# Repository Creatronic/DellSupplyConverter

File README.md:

# DellSupplyConverter
 Transform your old Dell charger to be usable on new Dell laptop
 
# About hardware
* PCB before 1.3 have been tested and are not ok against Dell connector footprint.
* V1.3 has not been tested yet (I hope it's the good one this time ...)
 
 # More infos
 https://blog.creatronic.fr/hacker-les-chargeurs-dell/

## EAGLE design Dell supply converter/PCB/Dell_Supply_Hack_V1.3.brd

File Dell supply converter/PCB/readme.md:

V1.0 and V1.1 => bad Dell connector footprint
V1.3 => not tested yet

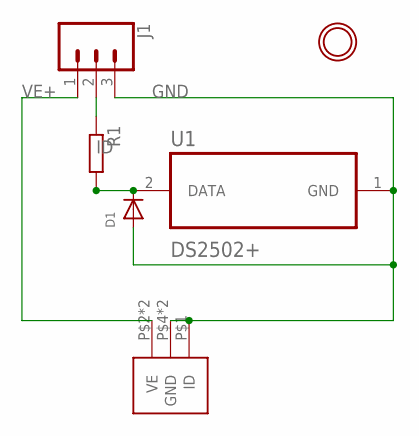
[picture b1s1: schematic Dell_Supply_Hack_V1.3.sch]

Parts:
D1: DIODESOD-323F; SOD-323F
J1: CONN_03LONGPADS; 1X03_LONGPADS
R1: R-EU_R0603; R0603
U1: DS2502+; TO92127P495H695-3
U$1: DELL_CON; DELL_CON_01
U$2: MOUNTING_HOLE; MOUNTINGHOLE_3.0_PLATED

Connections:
GND: D1.A, J1.3, U1.1 (GND), U$1.P$1 (ID), U$1.P$4 (GND), U$1.P$5 (GND)
ID: J1.2, R1.1
unnamed: D1.C, R1.2, U1.2 (DATA)
VE+: J1.1, U$1.P$2 (VE), U$1.P$3 (VE)

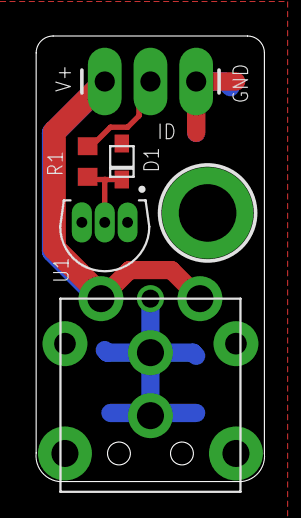
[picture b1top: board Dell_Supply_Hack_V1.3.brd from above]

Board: 2 copper layers, 12.7 x 24.8 mm, 6 parts (0 on the bottom side), 4 nets.

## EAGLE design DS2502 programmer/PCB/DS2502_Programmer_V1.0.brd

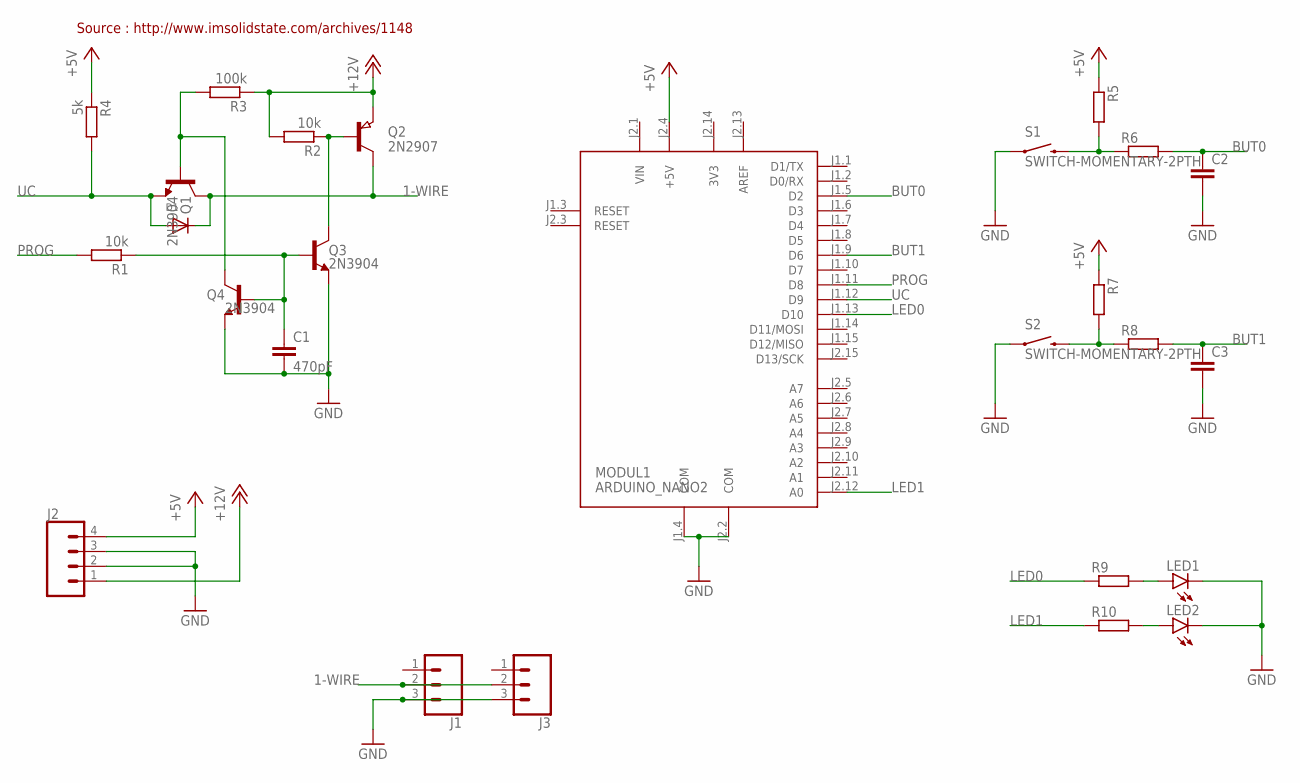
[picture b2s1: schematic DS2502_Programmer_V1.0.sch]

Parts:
C1: 470pF; C0603
C2, C3: C-EUC0603; C0603
D1: DIODESOD-523; SOD-523
J1, J3: CONN_03; 1X03
J2: CONN_04; 1X04
LED1, LED2: LEDCHIP-LED0805; CHIP-LED0805
MODUL1: ARDUINO_NANO2
Q1, Q3, Q4: 2N3904; SOT23-3
Q2: 2N2907; SOT23
R1, R2: 10k; R0603
R3: 100k; R0603
R4: 5k; R0603
R5, R6, R7, R8, R9, R10: R-EU_R0603; R0603
S1, S2: SWITCH-MOMENTARY-2PTH; TACTILE-PTH

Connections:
1-WIRE: D1.K (C), J1.2, J3.2, Q1.3 (C), Q2.3 (C)
3V3: MODUL1.J2.14 (3V3)
+5V: J2.4, MODUL1.J2.4 (+5V), R4.1, R5.1, R7.1
+12V: J2.1, Q2.2 (E), R2.2, R3.1
AREF: MODUL1.J2.13 (AREF)
BUT0: C2.1, MODUL1.J1.5 (D2), R6.2
BUT1: C3.1, MODUL1.J1.9 (D6), R8.2
GND: C1.2, C2.2, C3.2, J1.3, J2.2, J2.3, J3.3, LED1.C, LED2.C, MODUL1.J1.4 (COM), MODUL1.J2.2 (COM), Q3.2 (E), Q4.2 (E), S1.1, S2.1
LED0: MODUL1.J1.13 (D10), R9.1
LED1: MODUL1.J2.12 (A0), R10.1
unnamed: Q2.1 (B), Q3.3 (C), R2.1
unnamed: R5.2, R6.1, S1.3 (2)
unnamed: R7.2, R8.1, S2.3 (2)
unnamed: Q1.1 (B), Q4.3 (C), R3.2
unnamed: LED1.A, R9.2
unnamed: LED2.A, R10.2
unnamed: C1.1, Q3.1 (B), Q4.1 (B), R1.1
PROG: MODUL1.J1.11 (D8), R1.2
UC: D1.A, MODUL1.J1.12 (D9), Q1.2 (E), R4.2
VIN: MODUL1.J2.1 (VIN)

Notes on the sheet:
Source : http://www.imsolidstate.com/archives/1148

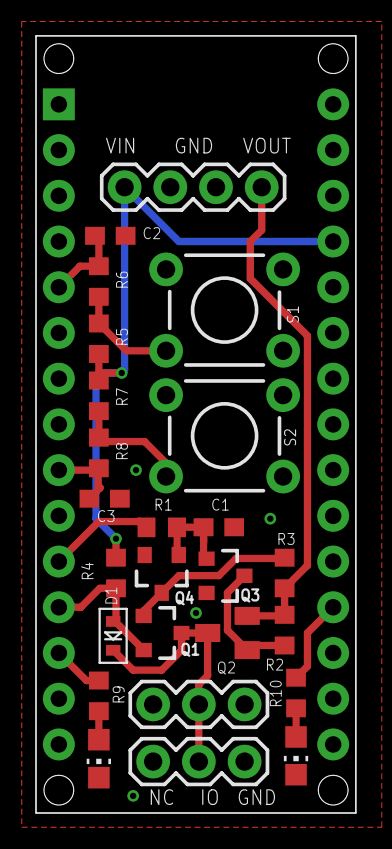
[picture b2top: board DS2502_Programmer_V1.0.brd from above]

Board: 2 copper layers, 17.8 x 43.2 mm, 28 parts (0 on the bottom side), 17 nets.

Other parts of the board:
U$1: CC_BY_NC_SA_1
U$3: CREATRONIC_4

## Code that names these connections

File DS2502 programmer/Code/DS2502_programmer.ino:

/*** Pin mapping ***/
#define PROG_PIN 8
#define ONEWIRE_PIN 9
#define BUTTON_0 2
#define BUTTON_1 6
#define LED0 10
#define LED1 A0

// This is the magic string Dell laptops need to see from the device in order to not go into limp home mode
// The interesting bit is the wattage 090 followed by the voltage 1950 and the amperage 4.6
char *progStr = "DELL00AC090195046CN09T";
#define ProgLocation (0x00)

#include <OneWire.h>

#define DS2502DevID 0x09

#define READ_ROM   0x33
#define MATCH_ROM  0x55
#define SKIP_ROM   0xCC
#define SEARCH_ROM 0xF0
#define ROM_SZ 8  // 8 bytes of laser etched ROM data , LSB = 0x09 == DS2502

// DS250x Memory commands -- can only be executed after one of the above ROM commands has been executed properly
#define READ_MEMORY  0xF0
#define READ_STATUS  0xAA
#define WRITE_STATUS 0x55
#define WRITE_MEMORY 0x0F

#define ProgPulseUs 500    // length of time 12V prog pulse needs to be applied for 

OneWire ds(ONEWIRE_PIN);             // OneWire bus on digital pin 6

void setup() {

  Serial.begin(115200);
  /*delay(2000);
    Serial.println("Hello !");*/
  pinMode(LED0, OUTPUT);
  pinMode(LED1, OUTPUT);

  pinMode(PROG_PIN, OUTPUT);
  digitalWrite(PROG_PIN, LOW);

  if (isDSPresent())
  {
    digitalWrite(LED1, HIGH);
    readStatus();
  }

}
void readStatus()
{

  byte leemem[12];

  Serial.println("Reading Status");

  ds.reset();
  ds.skip();                      // Skip ROM search, address the device no matter what
  leemem[0] = READ_STATUS;        // command
  leemem[1] = 0;       // low address byte
  leemem[2] = 0;                  // High address byte, always 0 for 2502
  ds.write(leemem[0], 1);       // Read data command, leave ghost power on
  ds.write(leemem[1], 1);       // LSB starting address, leave ghost power on
  ds.write(leemem[2], 1);       // MSB starting address, leave ghost power on

  byte crc = ds.read();             // DS250x generates a CRC for the command we sent, we assign a read slot and store it's value
  byte crc_calc = OneWire::crc8(leemem, 3);  // We calculate the CRC of the commands we sent using the library function and store it

  if (crc_calc != crc)        // Then we compare it to the value the ds250x calculated, if it fails, we print debug messages and abort
  {
    Serial.println("Invalid command CRC!");
    Serial.print("Calculated CRC:");
    Serial.println(crc_calc, HEX);   // HEX makes it easier to observe and compare
    Serial.print("DS250x readback CRC:");
    Serial.println(crc, HEX);
  }

  Serial.println("Status is: ");

  byte data[8];

  for (int i = 0; i < 8; i++)
  {
    data[i] = ds.read();
    Serial.print(data[i], HEX);
    Serial.print(" ");
  }
  Serial.println("");
}
void loop() {

  if (digitalRead(BUTTON_0) == LOW)
  {
    readDSMemory();
    while (digitalRead(BUTTON_0) == LOW);
    delay(100);
  }

  if (digitalRead(BUTTON_1) == LOW)
  {
    writeDSMemory();
    while (digitalRead(BUTTON_1) == LOW);
    delay(100);
  }
}

void readDSMemory()
{

  byte leemem[12];

  Serial.println("Reading Memory");

  ds.reset();
  ds.skip();                      // Skip ROM search, address the device no matter what
  leemem[0] = READ_MEMORY;        // command
  leemem[1] = ProgLocation;       // low address byte
  leemem[2] = 0;                  // High address byte, always 0 for 2502
  ds.write(leemem[0], 1);       // Read data command, leave ghost power on
  ds.write(leemem[1], 1);       // LSB starting address, leave ghost power on
  ds.write(leemem[2], 1);       // MSB starting address, leave ghost power on

  byte crc = ds.read();             // DS250x generates a CRC for the command we sent, we assign a read slot and store it's value
  byte crc_calc = OneWire::crc8(leemem, 3);  // We calculate the CRC of the commands we sent using the library function and store it

  if (crc_calc != crc)        // Then we compare it to the value the ds250x calculated, if it fails, we print debug messages and abort
  {
    Serial.println("Invalid command CRC!");
    Serial.print("Calculated CRC:");
    Serial.println(crc_calc, HEX);   // HEX makes it easier to observe and compare
    Serial.print("DS250x readback CRC:");
    Serial.println(crc, HEX);
  }

  Serial.println("Data is: ");

  byte data[32];

  for (int i = 0; i < 32; i++)
  {
    data[i] = ds.read();
    //Serial.print(data[i], HEX);
    Serial.write(data[i]);
    Serial.print(" ");
  }
  Serial.println("");
}

void writeDSMemory()
{

  uint8_t leemem[12];

  for (uint8_t i = 0; i < strlen(progStr); i++) {
    
    ds.reset();
    ds.skip();

    Serial.println("PROG Memory");

    leemem[0] = WRITE_MEMORY;       // command to initiate a write seq using array for later CRC calc
    leemem[2] = 0;                  // high address is always 0
    leemem[1] = ProgLocation + i;
    leemem[3] = (uint8_t)progStr[i];

    for(uint8_t i=0;i<4;i++)
    {
      ds.write(leemem[i]);
    }
    
    uint8_t crc = ds.read();

    uint8_t crc_calc = OneWire::crc8(leemem, 4);  // We calculate the CRC of the commands we sent using the library function and store it

    if (crc_calc != crc)        // Then we compare it to the value the ds250x calculated, if it fails, we print debug messages and abort
    {
      Serial.println("Invalid command CRC!");
      Serial.print("Calculated CRC:");
      Serial.println(crc_calc, HEX);   // HEX makes it easier to observe and compare
      Serial.print("DS250x readback CRC:");
      Serial.println(crc, HEX);
    }

    progPulse();
    
    uint8_t data = ds.read();
    
    Serial.print("Programmed data read back : ");
    Serial.print("adress=0x");
    Serial.print(leemem[1],HEX);
     Serial.print(" char=");
    Serial.write(data);
    Serial.print(" value=0x");
    Serial.println(data, HEX);

  }
}

byte isDSPresent()
{

  byte data[32];

  if (ds.reset())
  {

    Serial.println("device present");

    ds.write(READ_ROM, 1);
    Serial.println("ROM  Data is: ");
    for (int i = 0; i < 8; i++)
    {
      data[i] = ds.read();
      Serial.print(data[i], HEX);
      Serial.print(" ");
    }

    Serial.println(".");
    byte crc_calc = OneWire::crc8(data, 7);

    if (crc_calc == data[7] )
    {
      Serial.println("ROM CRC matches ");
      if (data[0] != DS2502DevID)
      {
        Serial.println("Device ID does not match DS2502");
      }
      return 1;
    }
    else
    {
      Serial.println("ROM CRC failed");
    }

  }
  return 0;
}

void progPulse()
{
  
  digitalWrite(PROG_PIN, HIGH);
  delayMicroseconds(ProgPulseUs);
  digitalWrite(PROG_PIN, LOW);
  delayMicroseconds(100);
  
}

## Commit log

2022-01-16 Add stl
2022-01-16 add photos
2022-01-16 Add gerbers + pcb
2022-04-06 add v1.3

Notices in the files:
parts and their libraries:
SparkFun-DiscreteSemi: Licensing: Creative Commons ShareAlike 4.0 International - https://creativecommons.org/licenses/by-sa/4.0
SparkFun: Licensing: CC v3.0 Share-Alike You are welcome to use this library for commercial purposes.
